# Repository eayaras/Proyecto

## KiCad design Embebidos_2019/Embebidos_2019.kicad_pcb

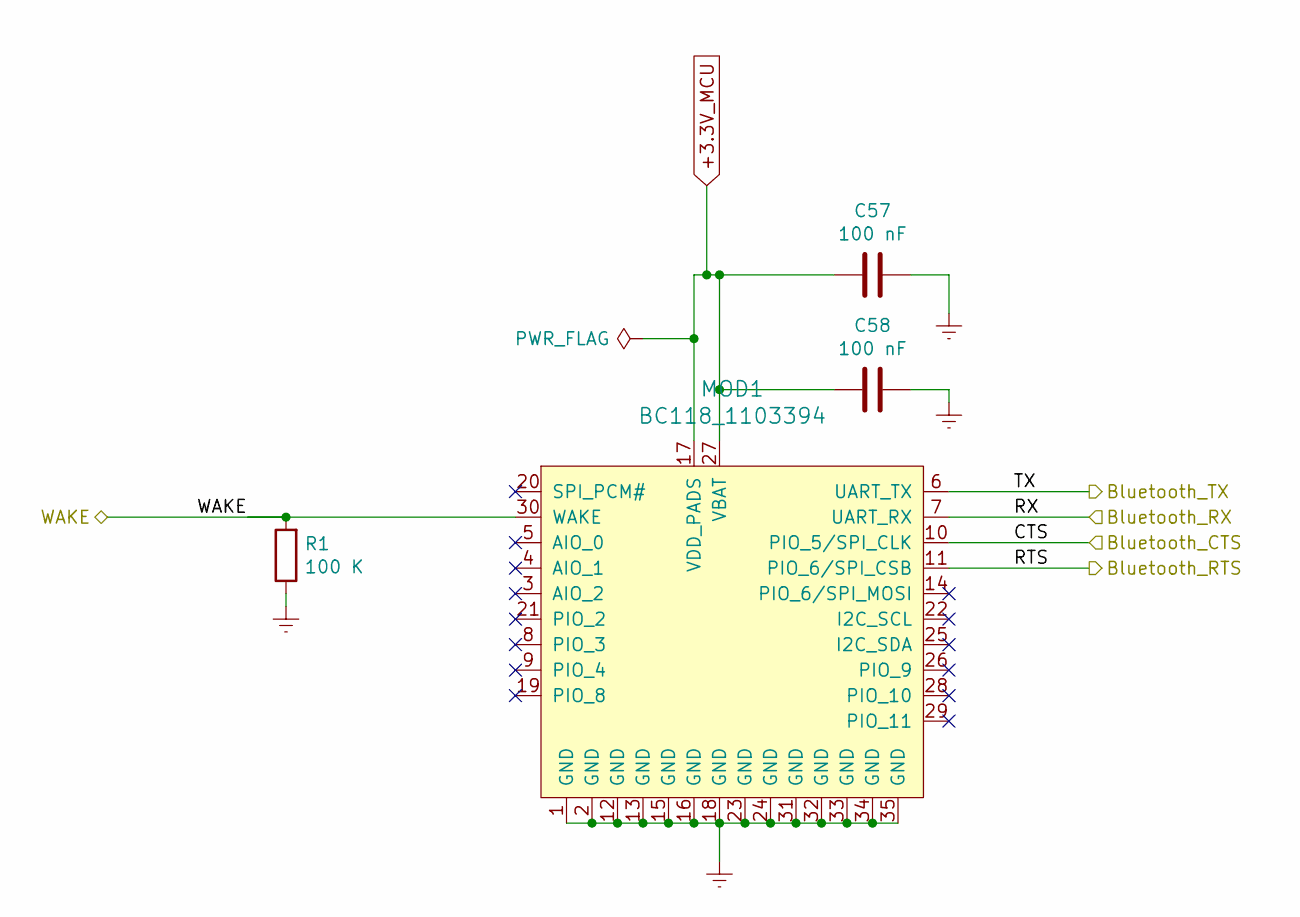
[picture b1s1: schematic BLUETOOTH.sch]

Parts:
C57, C58: 100 nF; C_0603_1608Metric_Pad1.05x0.95mm_HandSolder
MOD1: BC118_1103394; Bluetooth_Module_BC118; MPN BC118_1103394; Digi-Key_PN 1495-1003-1-ND
R1: 100 K; R_0603_1608Metric_Pad1.05x0.95mm_HandSolder

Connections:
+3.3V_MCU: C57.2, C58.2, MOD1.17 (VDD_PADS), MOD1.27 (VBAT); also elsewhere on the board
/BLUETOOTH/Bluetooth_RTS: MOD1.11 (PIO_6/SPI_CSB); also elsewhere on the board
/BLUETOOTH/Bluetooth_TX: MOD1.6 (UART_TX); also elsewhere on the board
/STM32/BL_WAKE: MOD1.30 (WAKE), R1.2; also elsewhere on the board
/STM32/UART1_TX: MOD1.7 (UART_RX); also elsewhere on the board
/STM32/UART_RTS: MOD1.10 (PIO_5/SPI_CLK); also elsewhere on the board
Earth: C57.1, C58.1, MOD1.1 (GND), MOD1.2 (GND), MOD1.12 (GND), MOD1.13 (GND), MOD1.15 (GND), MOD1.16 (GND), MOD1.18 (GND), MOD1.23 (GND), MOD1.24 (GND), MOD1.31 (GND), MOD1.32 (GND), MOD1.33 (GND), MOD1.34 (GND), MOD1.35 (GND), R1.1; also elsewhere on the board

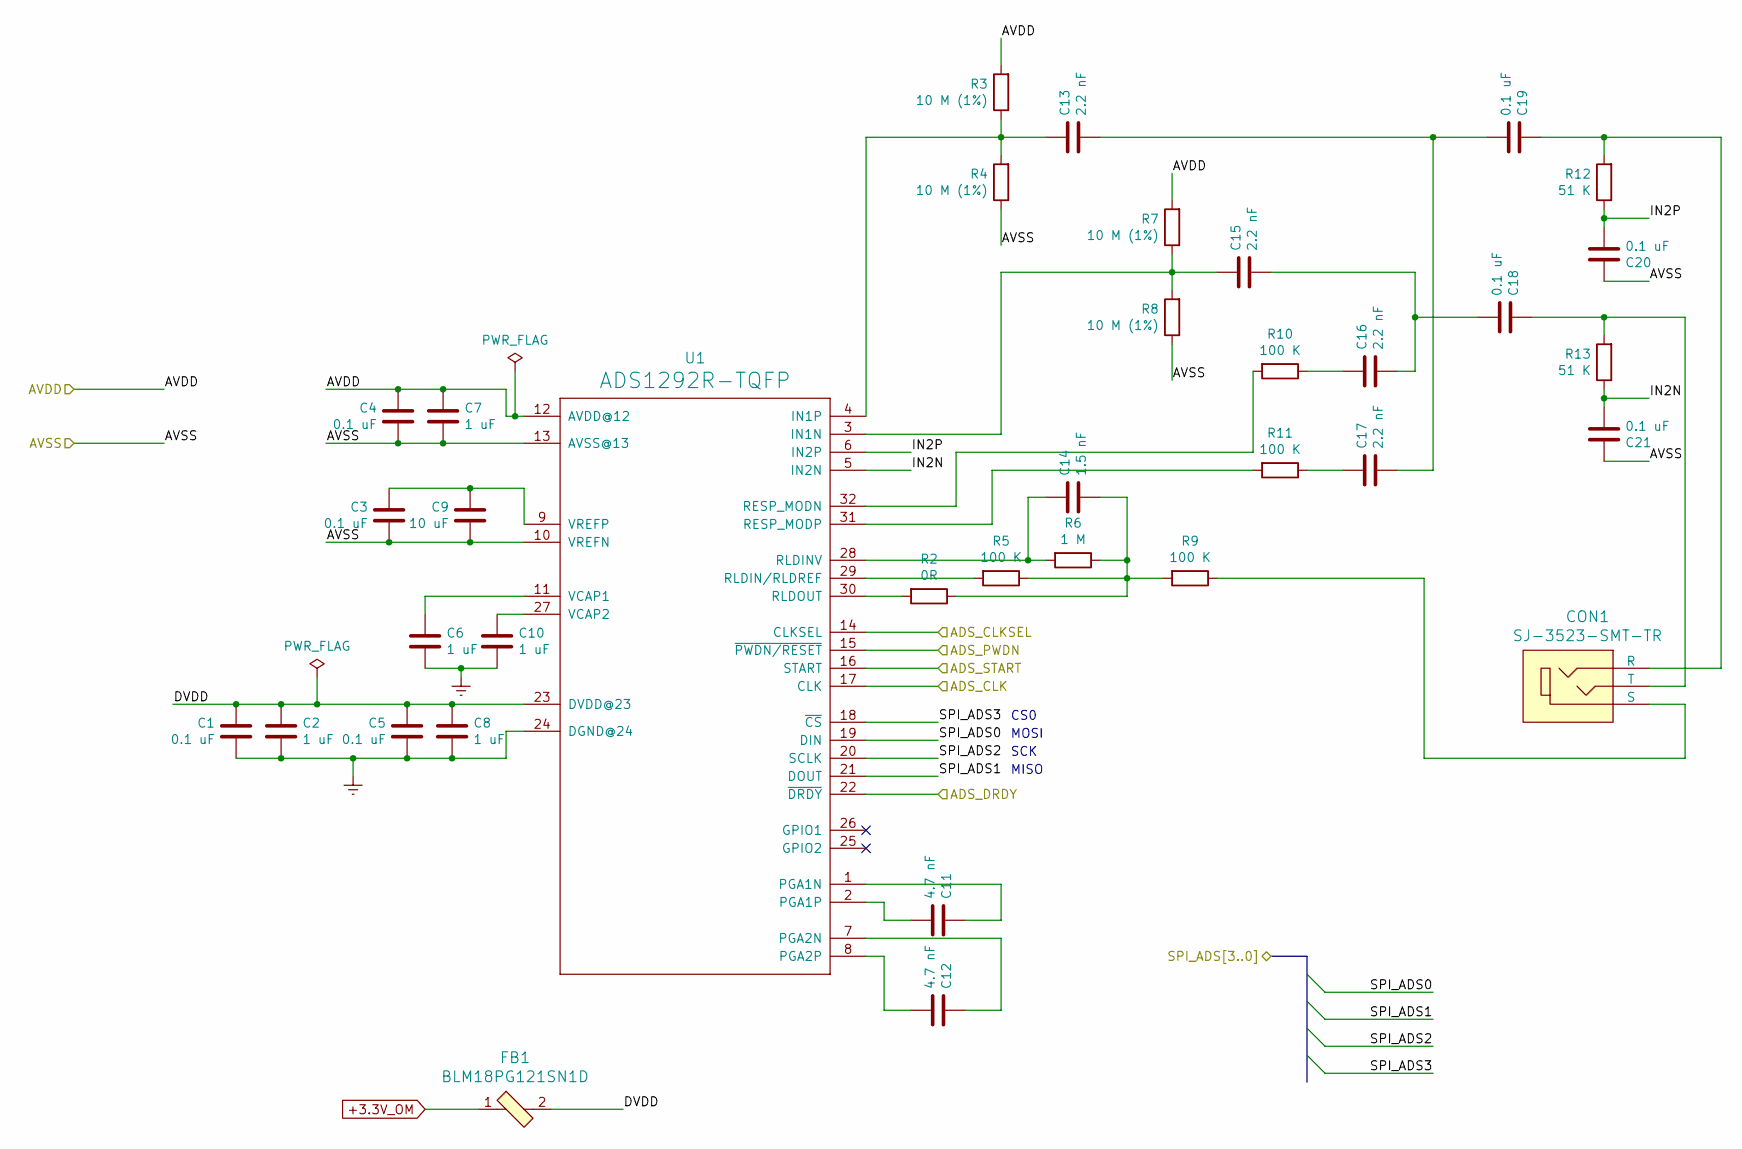
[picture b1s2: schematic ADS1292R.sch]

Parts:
C1, C3, C4, C5, C18, C19, C20, C21: 0.1 uF; C_0603_1608Metric_Pad1.05x0.95mm_HandSolder
C2, C6, C7, C8, C10: 1 uF; C_0603_1608Metric_Pad1.05x0.95mm_HandSolder
C9: 10 uF; C_0603_1608Metric_Pad1.05x0.95mm_HandSolder
C11, C12: 4.7 nF; C_0603_1608Metric_Pad1.05x0.95mm_HandSolder
C13, C15, C16, C17: 2.2 nF; C_0603_1608Metric_Pad1.05x0.95mm_HandSolder
C14: 1.5 nF; C_0603_1608Metric_Pad1.05x0.95mm_HandSolder
CON1: SJ-3523-SMT-TR; Switch_Slide_11.6x4mm_SJ-3523-SMT; MPN SJ-3523-SMT-TR; Digi-Key_PN CP-3523SJCT-ND
FB1: BLM18PG121SN1D; 0603; MPN BLM18PG121SN1D; Digi-Key_PN 490-1037-1-ND
R2: 0R; R_0603_1608Metric_Pad1.05x0.95mm_HandSolder
R3, R4, R7, R8: 10 M (1%); R_0603_1608Metric_Pad1.05x0.95mm_HandSolder
R5, R9, R10, R11: 100 K; R_0603_1608Metric_Pad1.05x0.95mm_HandSolder
R6: 1 M; R_0603_1608Metric_Pad1.05x0.95mm_HandSolder
R12, R13: 51 K; R_0603_1608Metric_Pad1.05x0.95mm_HandSolder
U1: ADS1292R-TQFP; TQFP-32_7x7mm_P0.8mm

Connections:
+3.3V_OM: FB1.1; also elsewhere on the board
/ADS1292R/AVDD: C4.1, C7.1, R3.2, R7.2, U1.12 (AVDD@12); also elsewhere on the board
/ADS1292R/DVDD: C1.1, C2.1, C5.1, C8.1, FB1.2, U1.23 (DVDD@23)
/ADS1292R/IN2N: C21.2, R13.1, U1.5 (IN2N)
/ADS1292R/IN2P: C20.2, R12.1, U1.6 (IN2P)
/ADS1292R/SPI_ADS0: U1.19 (DIN); also elsewhere on the board
/ADS1292R/SPI_ADS1: U1.21 (DOUT); also elsewhere on the board
/ADS1292R/SPI_ADS2: U1.20 (SCLK); also elsewhere on the board
/ADS1292R/SPI_ADS3: U1.18 (~CS); also elsewhere on the board
/STM32/A_CLK: U1.17 (CLK); also elsewhere on the board
/STM32/A_CLKSEL: U1.14 (CLKSEL); also elsewhere on the board
/STM32/A_DRY: U1.22 (~DRDY); also elsewhere on the board
/STM32/A_PWDN: U1.15 (~PWDN/RESET); also elsewhere on the board
/STM32/A_START: U1.16 (START); also elsewhere on the board
/SUPPLY/AVSS: C3.2, C4.2, C7.2, C9.2, C20.1, C21.1, R4.1, R8.1, U1.10 (VREFN), U1.13 (AVSS@13); also elsewhere on the board
Earth: C1.2, C2.2, C5.2, C6.2, C8.2, C10.2, U1.24 (DGND@24); also elsewhere on the board
unnamed: C3.1, C9.1, U1.9 (VREFP)
unnamed: C6.1, U1.11 (VCAP1)
unnamed: C10.1, U1.27 (VCAP2)
unnamed: C11.1, U1.1 (PGA1N)
unnamed: C11.2, U1.2 (PGA1P)
unnamed: C12.1, U1.7 (PGA2N)
unnamed: C12.2, U1.8 (PGA2P)
unnamed: C13.1, R3.1, R4.2, U1.4 (IN1P)
unnamed: C13.2, C17.2, C19.2
unnamed: C14.1, R6.2, U1.28 (RLDINV)
unnamed: C14.2, R2.1, R5.1, R6.1, R9.2
unnamed: C15.1, R7.1, R8.2, U1.3 (IN1N)
unnamed: C15.2, C16.2, C18.2
unnamed: C16.1, R10.1
unnamed: C17.1, R11.1
unnamed: C18.1, CON1.2 (T), R13.2
unnamed: C19.1, CON1.3 (R), R12.2
unnamed: CON1.1 (S), R9.1
unnamed: R2.2, U1.30 (RLDOUT)
unnamed: R5.2, U1.29 (RLDIN/RLDREF)
unnamed: R10.2, U1.32 (RESP_MODN)
unnamed: R11.2, U1.31 (RESP_MODP)

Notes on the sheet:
MOSI
MISO
SCK
CS0

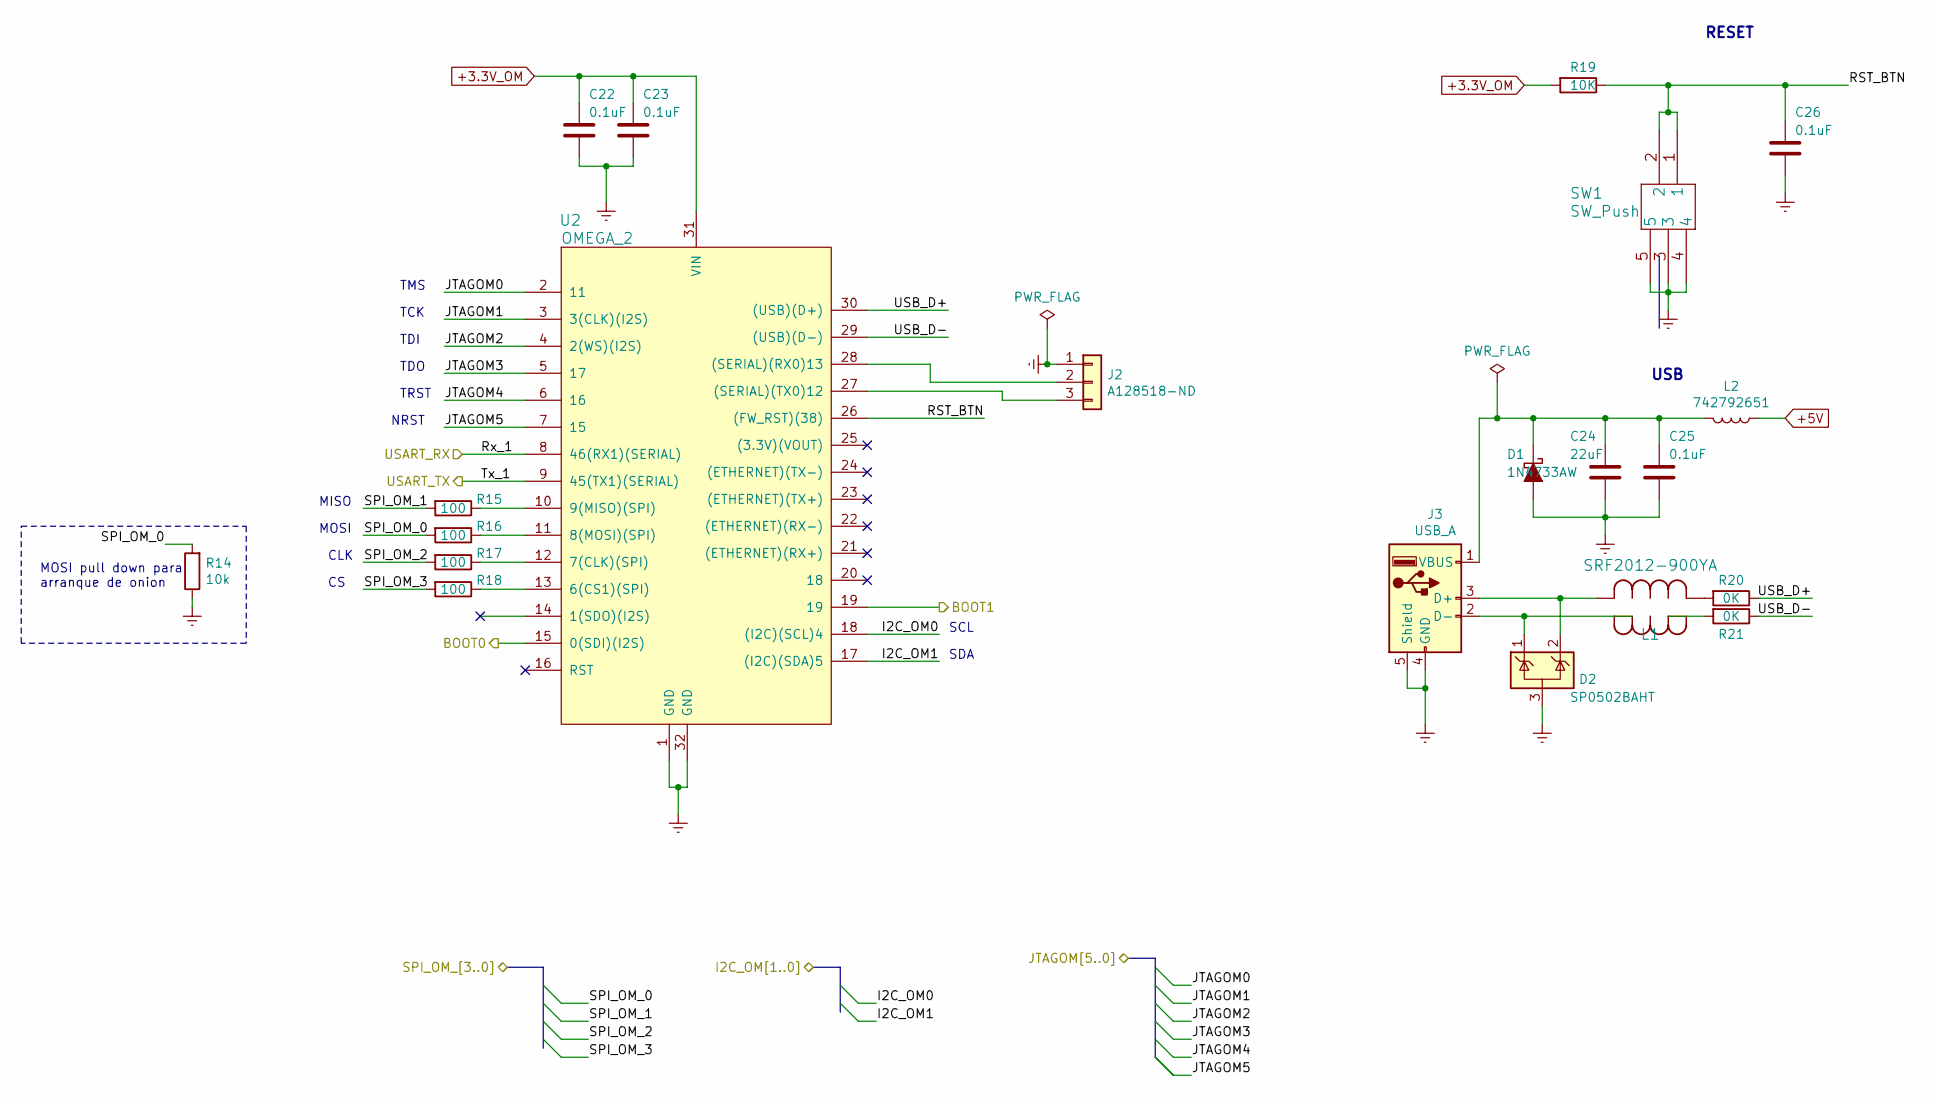
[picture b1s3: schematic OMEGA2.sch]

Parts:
C22, C23, C25, C26: 0.1uF; C_0603_1608Metric_Pad1.05x0.95mm_HandSolder
C24: 22uF; C_0805_HandSoldering
D1: 1N4733AW; D_SOD-123; DigiKey BZT52C5V1-TPMSCT-ND
D2: SP0502BAHT; SOT-23; DigiKey F2714CT-ND
J2: A128518-ND; PinHeader_1x03_P2.54mm_Vertical
J3: USB_A; Digikey 380-1412-ND
L1: SRF2012-900YA; DigiKey SRF2012-900YACT-ND
L2: 742792651; L_0603_1608Metric_Pad1.05x0.95mm_HandSolder; DigiKey 732-1593-1-ND
R14: 10k; C_0603_1608Metric_Pad1.05x0.95mm_HandSolder
R15, R17, R18: 100; R_0603_1608Metric_Pad1.05x0.95mm_HandSolder
R16: 100; C_0603_1608Metric_Pad1.05x0.95mm_HandSolder
R19: 10K; R_0603_1608Metric_Pad1.05x0.95mm_HandSolder
R20, R21: 0K; R_0603_1608Metric_Pad1.05x0.95mm_HandSolder
SW1: SW_Push; FSM1LPTR; DigiKey 450-1756-1-ND
U2: OMEGA_2; ONION-OMEGA

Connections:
+3.3V_OM: C22.1, C23.1, R19.2, U2.31 (VIN); also elsewhere on the board
+5V: L2.1; also elsewhere on the board
/OMEGA2/BOOT0: U2.15 (0(SDI)(I2S)); also elsewhere on the board
/OMEGA2/BOOT1: U2.19; also elsewhere on the board
/OMEGA2/I2C_OM0: U2.18 ((I2C)(SCL)4); also elsewhere on the board
/OMEGA2/I2C_OM1: U2.17 ((I2C)(SDA)5); also elsewhere on the board
/OMEGA2/RST_BTN: C26.1, R19.1, SW1.1, SW1.2, U2.26 ((FW_RST)(38))
/OMEGA2/USART_TX: U2.9 (45(TX1)(SERIAL)); also elsewhere on the board
/OMEGA2/USB_D+: R20.1, U2.30 ((USB)(D+))
/OMEGA2/USB_D-: R21.1, U2.29 ((USB)(D-))
/STM32/JTAG0: U2.2 (11); also elsewhere on the board
/STM32/JTAG1: U2.3 (3(CLK)(I2S)); also elsewhere on the board
/STM32/JTAG2: U2.4 (2(WS)(I2S)); also elsewhere on the board
/STM32/JTAG3: U2.5 (17); also elsewhere on the board
/STM32/JTAG4: U2.6 (16); also elsewhere on the board
/STM32/JTAG5: U2.7 (15); also elsewhere on the board
/STM32/SPI1_U0: R14.2, R16.2; also elsewhere on the board
/STM32/SPI1_U1: R15.2; also elsewhere on the board
/STM32/SPI1_U2: R17.2; also elsewhere on the board
/STM32/SPI1_U3: R18.2; also elsewhere on the board
/STM32/UART2_TX: U2.8 (46(RX1)(SERIAL)); also elsewhere on the board
Earth: C22.2, C23.2, C24.2, C25.2, C26.2, D1.2 (A), D2.3 (A), J2.1, J3.4 (GND), J3.5 (Shield), R14.1, SW1.3, SW1.4, SW1.5, U2.1 (GND), U2.32 (GND); also elsewhere on the board
unnamed: C24.1, C25.1, D1.1 (K), J3.1 (VBUS), L2.2
unnamed: D2.1 (K), J3.2 (D-), L1.4
unnamed: D2.2 (K), J3.3 (D+), L1.1
unnamed: J2.2, U2.28 ((SERIAL)(RX0)13)
unnamed: J2.3, U2.27 ((SERIAL)(TX0)12)
unnamed: L1.2, R20.2
unnamed: L1.3, R21.2
unnamed: R15.1, U2.10 (9(MISO)(SPI))
unnamed: R16.1, U2.11 (8(MOSI)(SPI))
unnamed: R17.1, U2.12 (7(CLK)(SPI))
unnamed: R18.1, U2.13 (6(CS1)(SPI))

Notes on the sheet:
USB
RESET
MOSI pull down para arranque de onion
MOSI
MISO
CLK
SCL
SDA
TMS
TCK
TDI
TDO
TRST
NRST

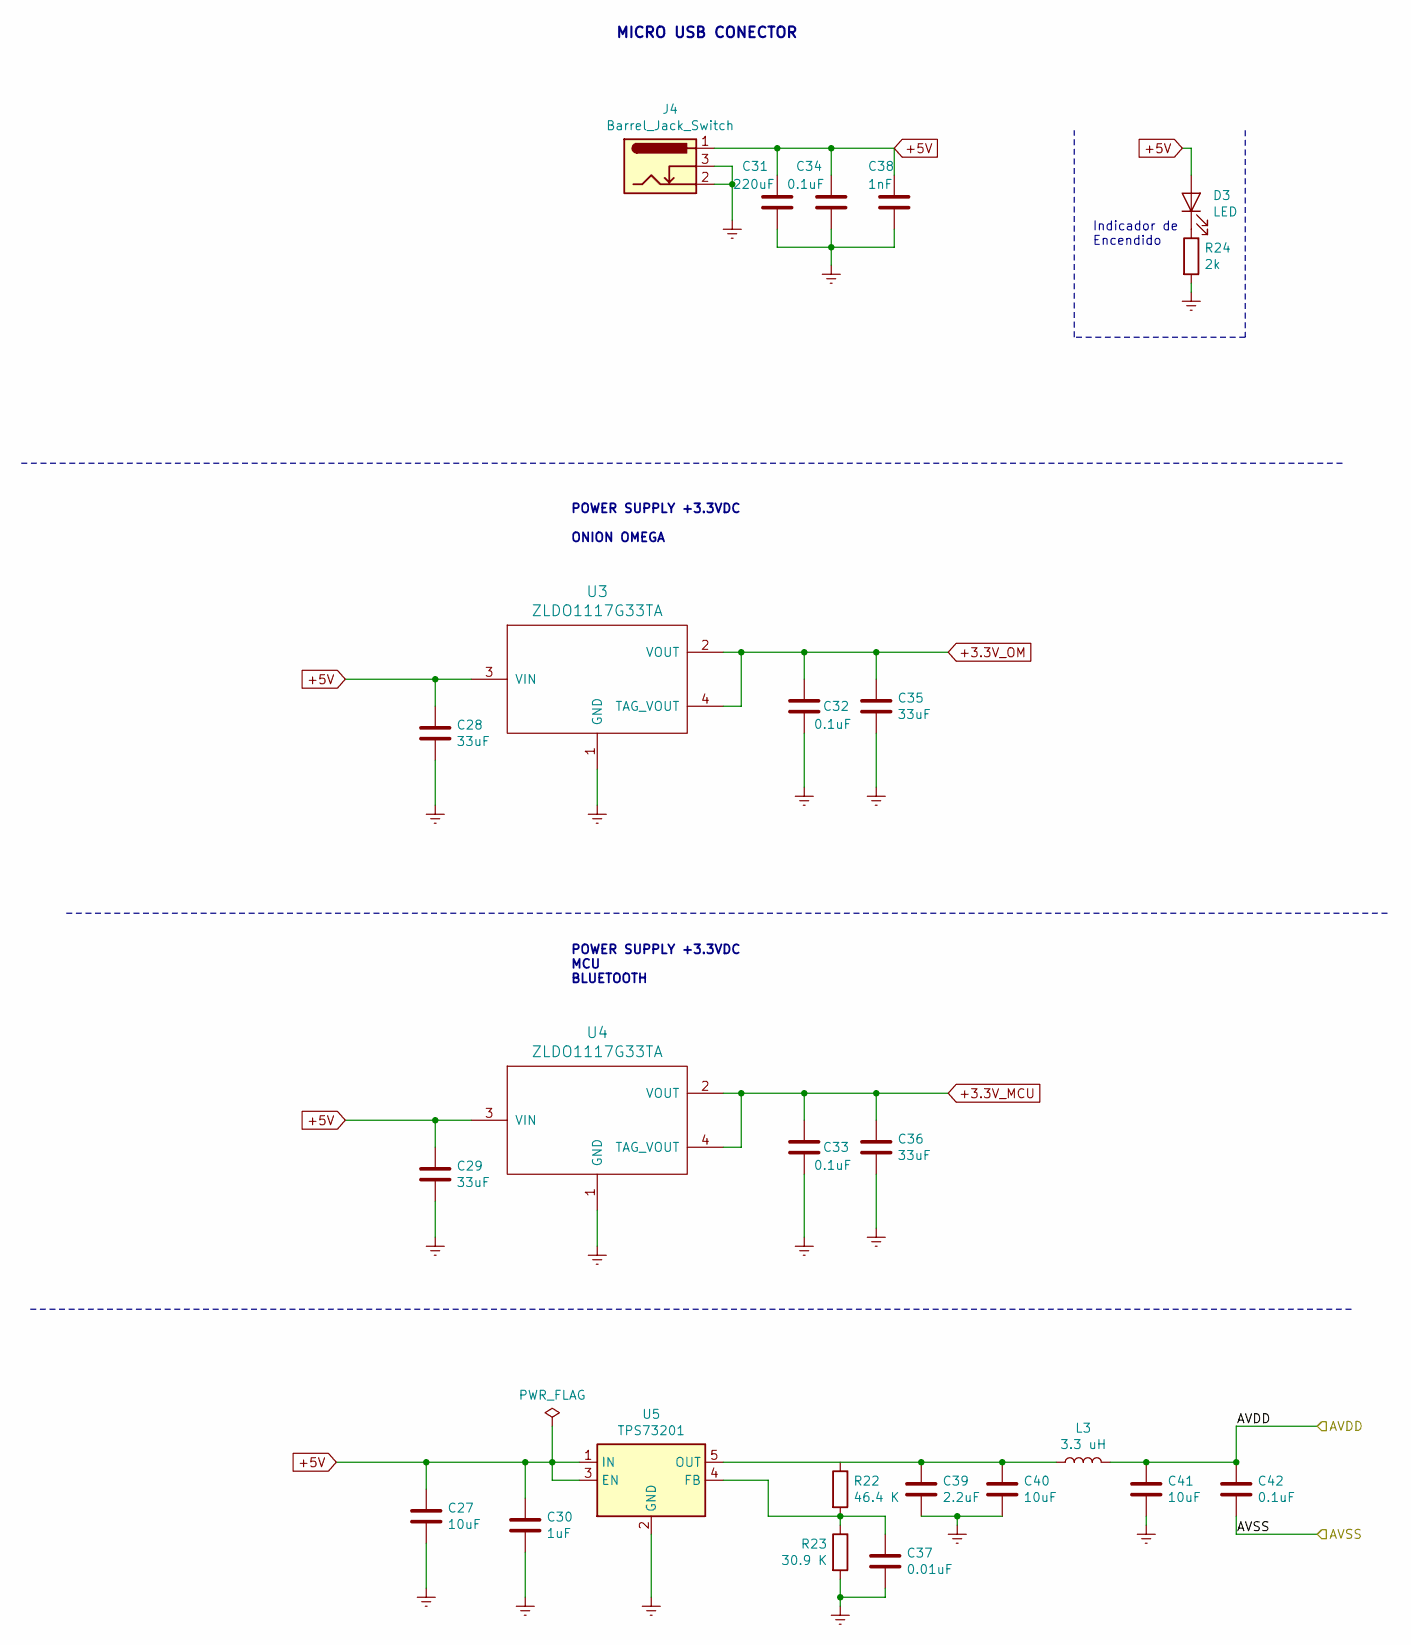
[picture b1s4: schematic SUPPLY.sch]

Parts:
C27: 10uF; C_1206_3216Metric_Pad1.42x1.75mm_HandSolder
C28, C29, C35, C36: 33uF; C_1206_3216Metric_Pad1.42x1.75mm_HandSolder
C30: 1uF; C_0603_1608Metric_Pad1.05x0.95mm_HandSolder
C31: 220uF; C_1206_3216Metric_Pad1.42x1.75mm_HandSolder
C32, C33, C34, C42: 0.1uF; C_0603_1608Metric_Pad1.05x0.95mm_HandSolder
C37: 0.01uF; C_0603_1608Metric_Pad1.05x0.95mm_HandSolder
C38: 1nF; C_0603_1608Metric_Pad1.05x0.95mm_HandSolder
C39: 2.2uF; C_0603_1608Metric_Pad1.05x0.95mm_HandSolder
C40, C41: 10uF; C_0603_1608Metric_Pad1.05x0.95mm_HandSolder
D3: LED; LED_0805_HandSoldering
J4: Barrel_Jack_Switch; BARREL_JACK; DigiKey CP-002A-ND
L3: 3.3 uH; L_0603_1608Metric_Pad1.05x0.95mm_HandSolder
R22: 46.4 K; R_0603_1608Metric_Pad1.05x0.95mm_HandSolder
R23: 30.9 K; R_0603_1608Metric_Pad1.05x0.95mm_HandSolder
R24: 2k; R_0603_1608Metric_Pad1.05x0.95mm_HandSolder
U3, U4: ZLDO1117G33TA; SOT-223; DigiKey ZLDO1117G33DICT-ND
U5: TPS73201; SOT-23-5

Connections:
+3.3V_MCU: C33.1, C36.1, U4.2 (VOUT), U4.4 (TAG_VOUT); also elsewhere on the board
+3.3V_OM: C32.1, C35.1, U3.2 (VOUT), U3.4 (TAG_VOUT); also elsewhere on the board
+5V: C27.1, C28.1, C29.1, C30.1, C31.1, C34.1, C38.1, D3.2 (A), J4.1, U3.3 (VIN), U4.3 (VIN), U5.1 (IN), U5.3 (EN); also elsewhere on the board
/ADS1292R/AVDD: C41.1, C42.1, L3.2; also elsewhere on the board
/SUPPLY/AVSS: C42.2; also elsewhere on the board
Earth: C27.2, C28.2, C29.2, C30.2, C31.2, C32.2, C33.2, C34.2, C35.2, C36.2, C37.2, C38.2, C39.2, C40.2, C41.2, J4.2, J4.3, R23.2, R24.2, U3.1 (GND), U4.1 (GND), U5.2 (GND); also elsewhere on the board
unnamed: C37.1, R22.2, R23.1, U5.4 (FB)
unnamed: D3.1 (K), R24.1

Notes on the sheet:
POWER SUPPLY +3.3VDC ONION OMEGA
MICRO USB CONECTOR
Indicador de Encendido
POWER SUPPLY +3.3VDC MCU BLUETOOTH

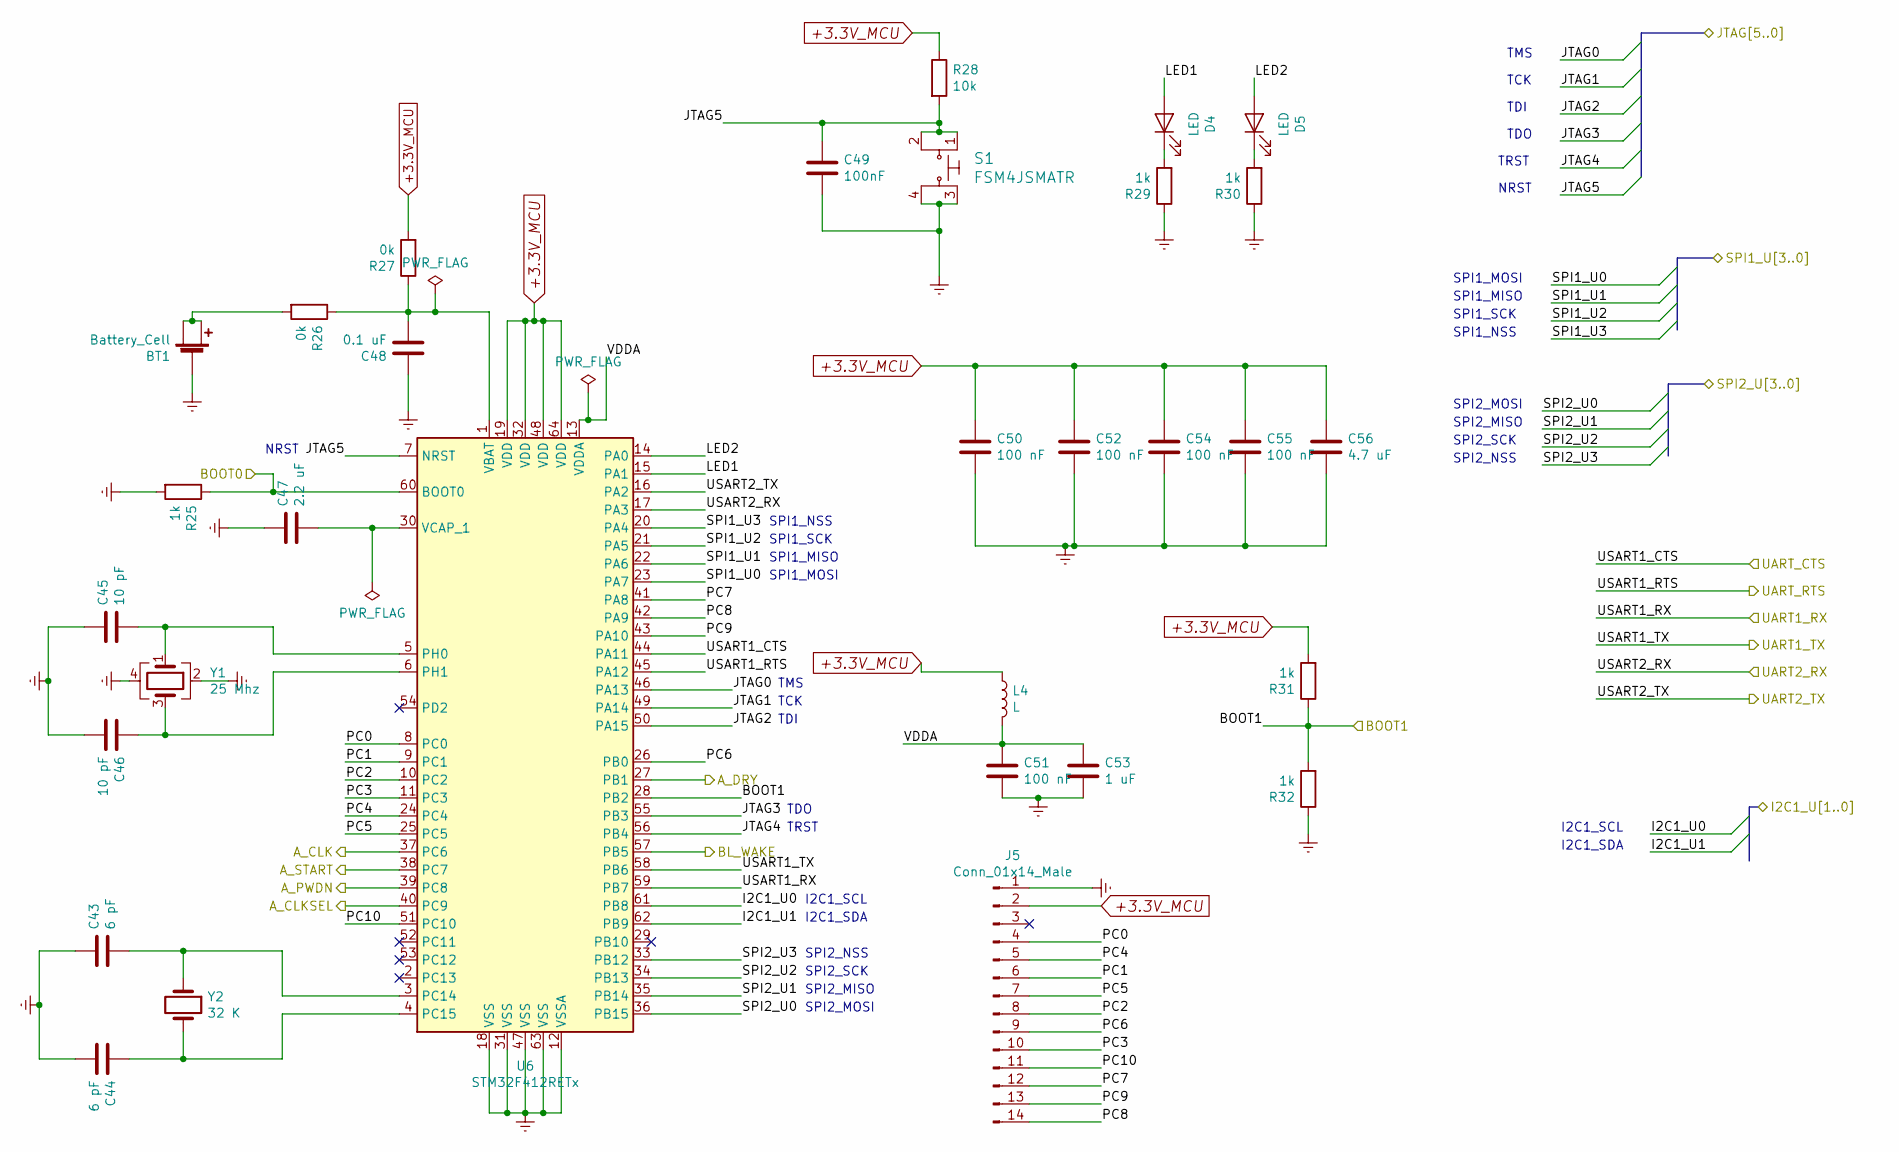
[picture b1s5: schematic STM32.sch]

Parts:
BT1: Battery_Cell; BAT-HLD-001
C43, C44: 6 pF; C_0603_1608Metric_Pad1.05x0.95mm_HandSolder
C45, C46: 10 pF; C_0603_1608Metric_Pad1.05x0.95mm_HandSolder
C47: 2.2 uF; C_0603_1608Metric_Pad1.05x0.95mm_HandSolder
C48: 0.1 uF; C_0603_1608Metric_Pad1.05x0.95mm_HandSolder
C49: 100nF; C_0603_1608Metric_Pad1.05x0.95mm_HandSolder
C50, C51, C52, C54, C55: 100 nF; C_0603_1608Metric_Pad1.05x0.95mm_HandSolder
C53: 1 uF; C_0603_1608Metric_Pad1.05x0.95mm_HandSolder
C56: 4.7 uF; C_0603_1608Metric_Pad1.05x0.95mm_HandSolder
D4, D5: LED; LED_0805_2012Metric_Pad1.15x1.40mm_HandSolder
J5: Conn_01x14_Male; PinHeader_2x07_P2.54mm_Vertical
L4: L; L_0603_1608Metric_Pad1.05x0.95mm_HandSolder
R25, R29, R30, R31, R32: 1k; R_0603_1608Metric_Pad1.05x0.95mm_HandSolder
R26, R27: 0k; R_0603_1608Metric_Pad1.05x0.95mm_HandSolder
R28: 10k; R_0603_1608Metric_Pad1.05x0.95mm_HandSolder
S1: FSM4JSMATR; Switch_Tactile_SMD_6x6mm; MPN FSM4JSMATR; Digi-Key_PN 450-1759-1-ND
U6: STM32F412RETx; LQFP-64_10x10mm_P0.5mm
Y1: 25 Mhz; Crystal_SMD_Abracon_ABM8G-4Pin_3.2x2.5mm
Y2: 32 K; NX3215SA

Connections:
+3.3V_MCU: C50.1, C52.1, C54.1, C55.1, C56.1, J5.2, L4.1, R27.2, R28.1, R31.2, U6.19 (VDD), U6.32 (VDD), U6.48 (VDD), U6.64 (VDD); also elsewhere on the board
/ADS1292R/SPI_ADS0: U6.36 (PB15); also elsewhere on the board
/ADS1292R/SPI_ADS1: U6.35 (PB14); also elsewhere on the board
/ADS1292R/SPI_ADS2: U6.34 (PB13); also elsewhere on the board
/ADS1292R/SPI_ADS3: U6.33 (PB12); also elsewhere on the board
/BLUETOOTH/Bluetooth_RTS: U6.44 (PA11); also elsewhere on the board
/BLUETOOTH/Bluetooth_TX: U6.59 (PB7); also elsewhere on the board
/OMEGA2/BOOT0: R25.1, U6.60 (BOOT0); also elsewhere on the board
/OMEGA2/BOOT1: R31.1, R32.2, U6.28 (PB2); also elsewhere on the board
/OMEGA2/I2C_OM0: U6.61 (PB8); also elsewhere on the board
/OMEGA2/I2C_OM1: U6.62 (PB9); also elsewhere on the board
/OMEGA2/USART_TX: U6.17 (PA3); also elsewhere on the board
/STM32/A_CLK: U6.37 (PC6); also elsewhere on the board
/STM32/A_CLKSEL: U6.40 (PC9); also elsewhere on the board
/STM32/A_DRY: U6.27 (PB1); also elsewhere on the board
/STM32/A_PWDN: U6.39 (PC8); also elsewhere on the board
/STM32/A_START: U6.38 (PC7); also elsewhere on the board
/STM32/BL_WAKE: U6.57 (PB5); also elsewhere on the board
/STM32/JTAG0: U6.46 (PA13); also elsewhere on the board
/STM32/JTAG1: U6.49 (PA14); also elsewhere on the board
/STM32/JTAG2: U6.50 (PA15); also elsewhere on the board
/STM32/JTAG3: U6.55 (PB3); also elsewhere on the board
/STM32/JTAG4: U6.56 (PB4); also elsewhere on the board
/STM32/JTAG5: C49.1, R28.2, S1.1, S1.2, U6.7 (NRST); also elsewhere on the board
/STM32/LED1: D4.2 (A), U6.15 (PA1)
/STM32/LED2: D5.2 (A), U6.14 (PA0)
/STM32/PC0: J5.4, U6.8 (PC0)
/STM32/PC1: J5.6, U6.9 (PC1)
/STM32/PC2: J5.8, U6.10 (PC2)
/STM32/PC3: J5.10, U6.11 (PC3)
/STM32/PC4: J5.5, U6.24 (PC4)
/STM32/PC5: J5.7, U6.25 (PC5)
/STM32/PC6: J5.9, U6.26 (PB0)
/STM32/PC7: J5.12, U6.41 (PA8)
/STM32/PC8: J5.14, U6.42 (PA9)
/STM32/PC9: J5.13, U6.43 (PA10)
/STM32/PC10: J5.11, U6.51 (PC10)
/STM32/SPI1_U0: U6.23 (PA7); also elsewhere on the board
/STM32/SPI1_U1: U6.22 (PA6); also elsewhere on the board
/STM32/SPI1_U2: U6.21 (PA5); also elsewhere on the board
/STM32/SPI1_U3: U6.20 (PA4); also elsewhere on the board
/STM32/UART1_TX: U6.58 (PB6); also elsewhere on the board
/STM32/UART2_TX: U6.16 (PA2); also elsewhere on the board
/STM32/UART_RTS: U6.45 (PA12); also elsewhere on the board
/STM32/VDDA: C51.1, C53.1, L4.2, U6.13 (VDDA)
Earth: BT1.2 (-), C43.1, C44.2, C45.1, C46.2, C47.1, C48.1, C49.2, C50.2, C51.2, C52.2, C53.2, C54.2, C55.2, C56.2, J5.1, R25.2, R29.1, R30.1, R32.1, S1.3, S1.4, U6.12 (VSSA), U6.18 (VSS), U6.31 (VSS), U6.47 (VSS), U6.63 (VSS), Y1.2, Y1.4; also elsewhere on the board
unnamed: BT1.1 (+), BT1.3 (+), R26.2
unnamed: C43.2, U6.3 (PC14), Y2.1
unnamed: C44.1, U6.4 (PC15), Y2.2
unnamed: C45.2, U6.5 (PH0), Y1.1
unnamed: C46.1, U6.6 (PH1), Y1.3
unnamed: C47.2, U6.30 (VCAP_1)
unnamed: C48.2, R26.1, R27.1, U6.1 (VBAT)
unnamed: D4.1 (K), R29.2
unnamed: D5.1 (K), R30.2

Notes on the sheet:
TMS
TCK
TDI
TRST
NRST
TDO
SPI1_MOSI
SPI1_MISO
SPI1_SCK
SPI1_NSS
SPI2_MOSI
SPI2_MISO
SPI2_SCK
SPI2_NSS
I2C1_SCL
I2C1_SDA

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
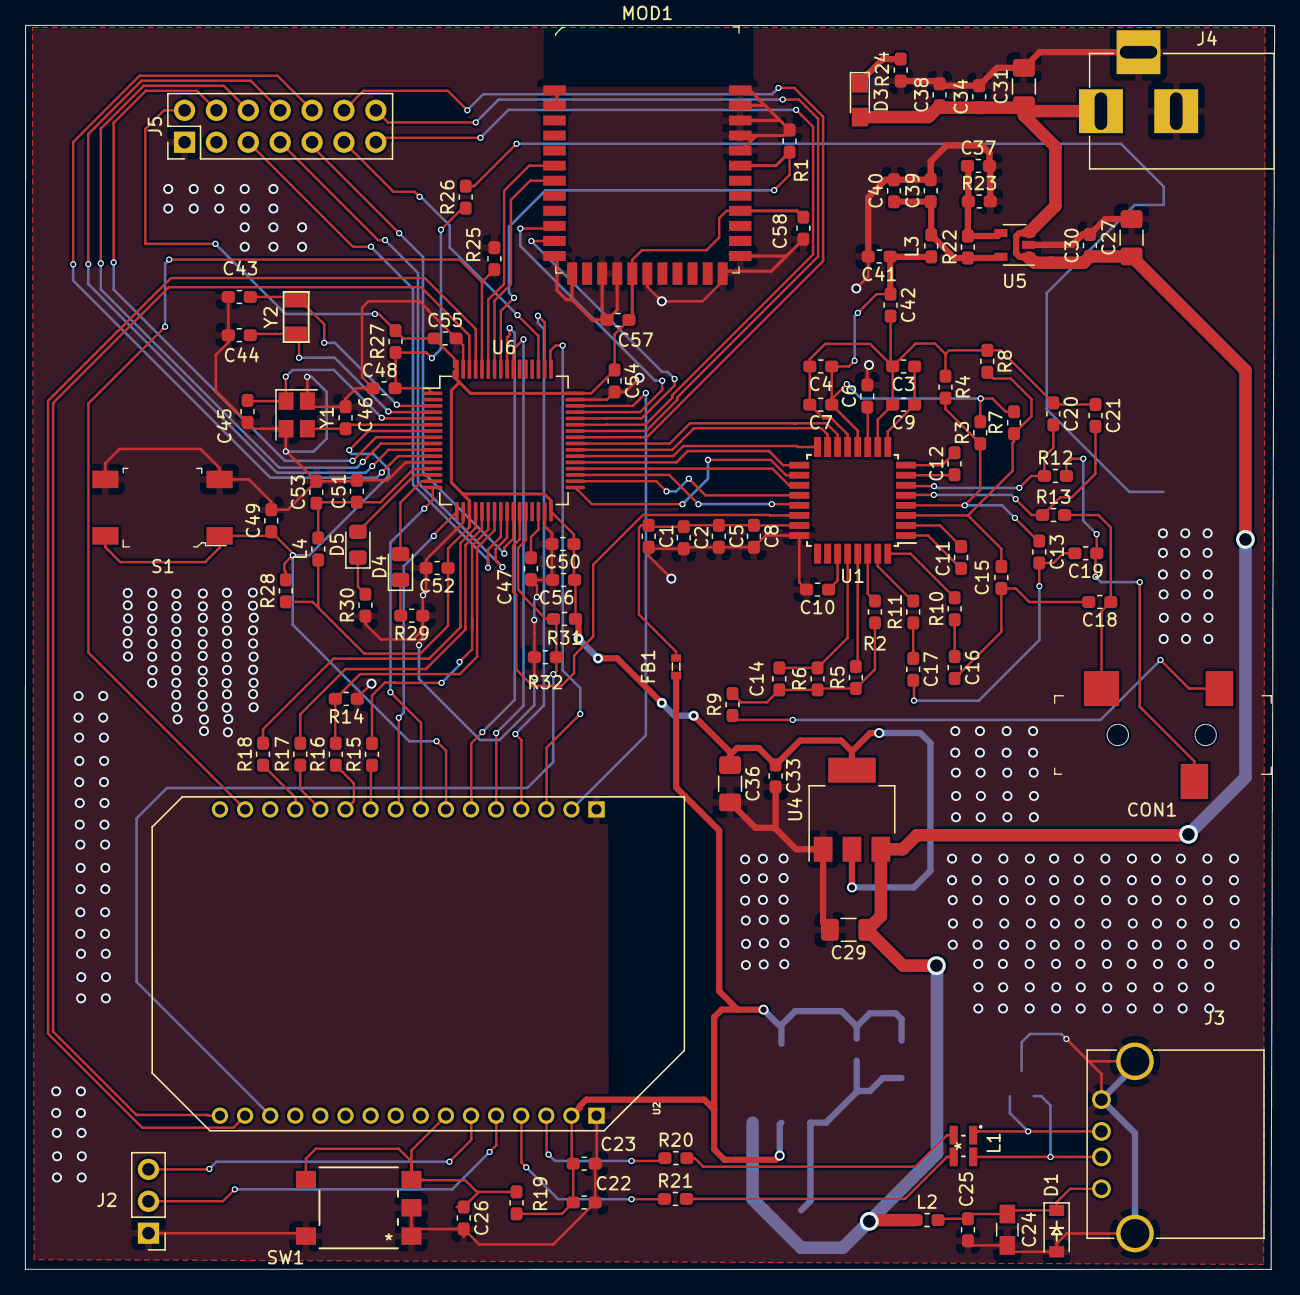
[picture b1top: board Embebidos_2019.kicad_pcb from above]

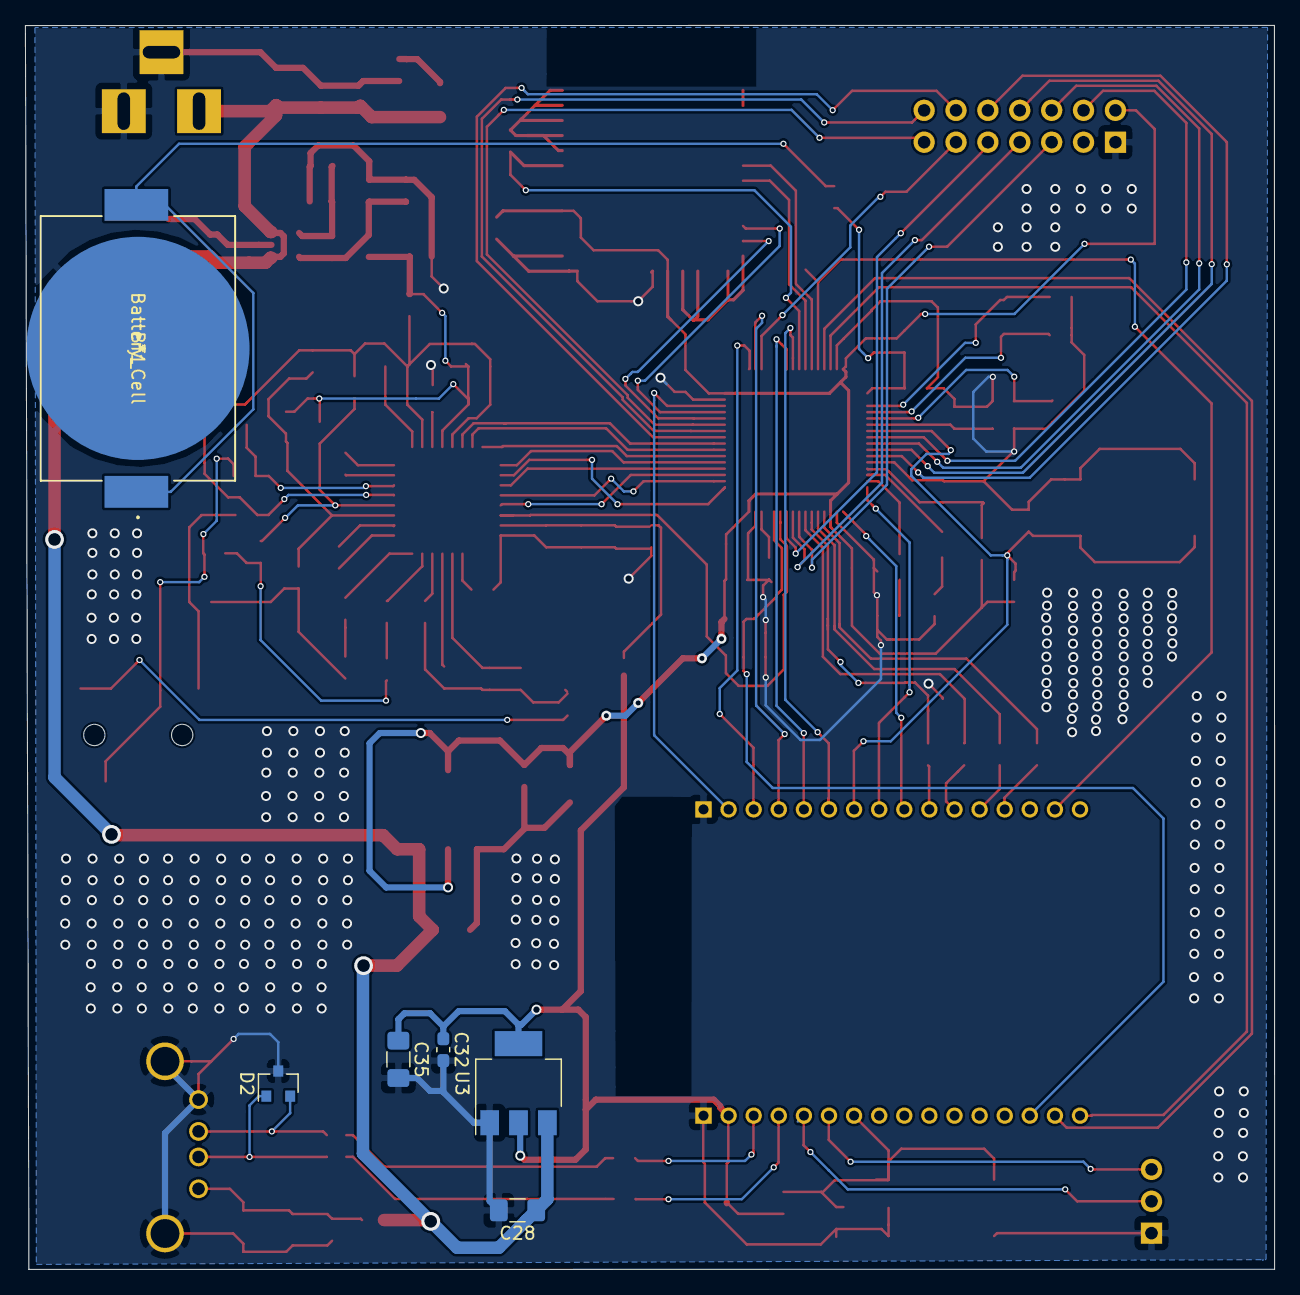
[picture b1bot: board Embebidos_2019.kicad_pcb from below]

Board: 2 copper layers, 99.5 x 99.1 mm, 117 parts (6 on the bottom side), 101 nets.

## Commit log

2019-06-02 los archivos ya fueron modificados
2019-06-02 los archivos ya fueron modificados, por fin subio
2019-06-02 Bueno esto casi me saca canas, esta es la ultima version ya puedes editar
2019-06-06 ultima version

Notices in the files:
parts and their libraries:
Copyright 2016 Accelerated Designs. All rights reserved.
